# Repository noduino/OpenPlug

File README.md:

Noduino Open Plug
=======================================

[*Noduino Open Plug (OpenPlug V0.8)*](https://wiki.jackslab.org/Noduino_OpenPlug/)

[*Noduino Open Plug (OpenPlug V0.8)*](https://wiki.jackslab.org/Noduino_OpenPlug/)

Overview
-------------------

* AC 85V - 250V WiFi Smart Plug
* ESP8285 inside
* 250V 10A relay
* Shell size 53mm x 53mm x 27mm

Shell
-------------------

* https://detail.1688.com/offer/520959590805.html

WiFi Module
-------------------

[*Noduino NodeC WiFi Module*](https://wiki.jackslab.org/Noduino_SmartNode)

SCH
-------------------

[*Noduino Open Plug (OpenPlug V0.8)*](https://wiki.jackslab.org/Noduino_OpenPlug/)

Layout
-------------------

[*Noduino Open Plug (OpenPlug V0.8)*](https://wiki.jackslab.org/Noduino_OpenPlug/)

WiKi
-------------------

* http://wiki.jackslab.org/Noduino_OpenPlug

License Information
-------------------
The hardware is released under [Creative Commons ShareAlike 4.0 International](https://creativecommons.org/licenses/by-sa/4.0/).

Distributed as-is; no warranty is given.

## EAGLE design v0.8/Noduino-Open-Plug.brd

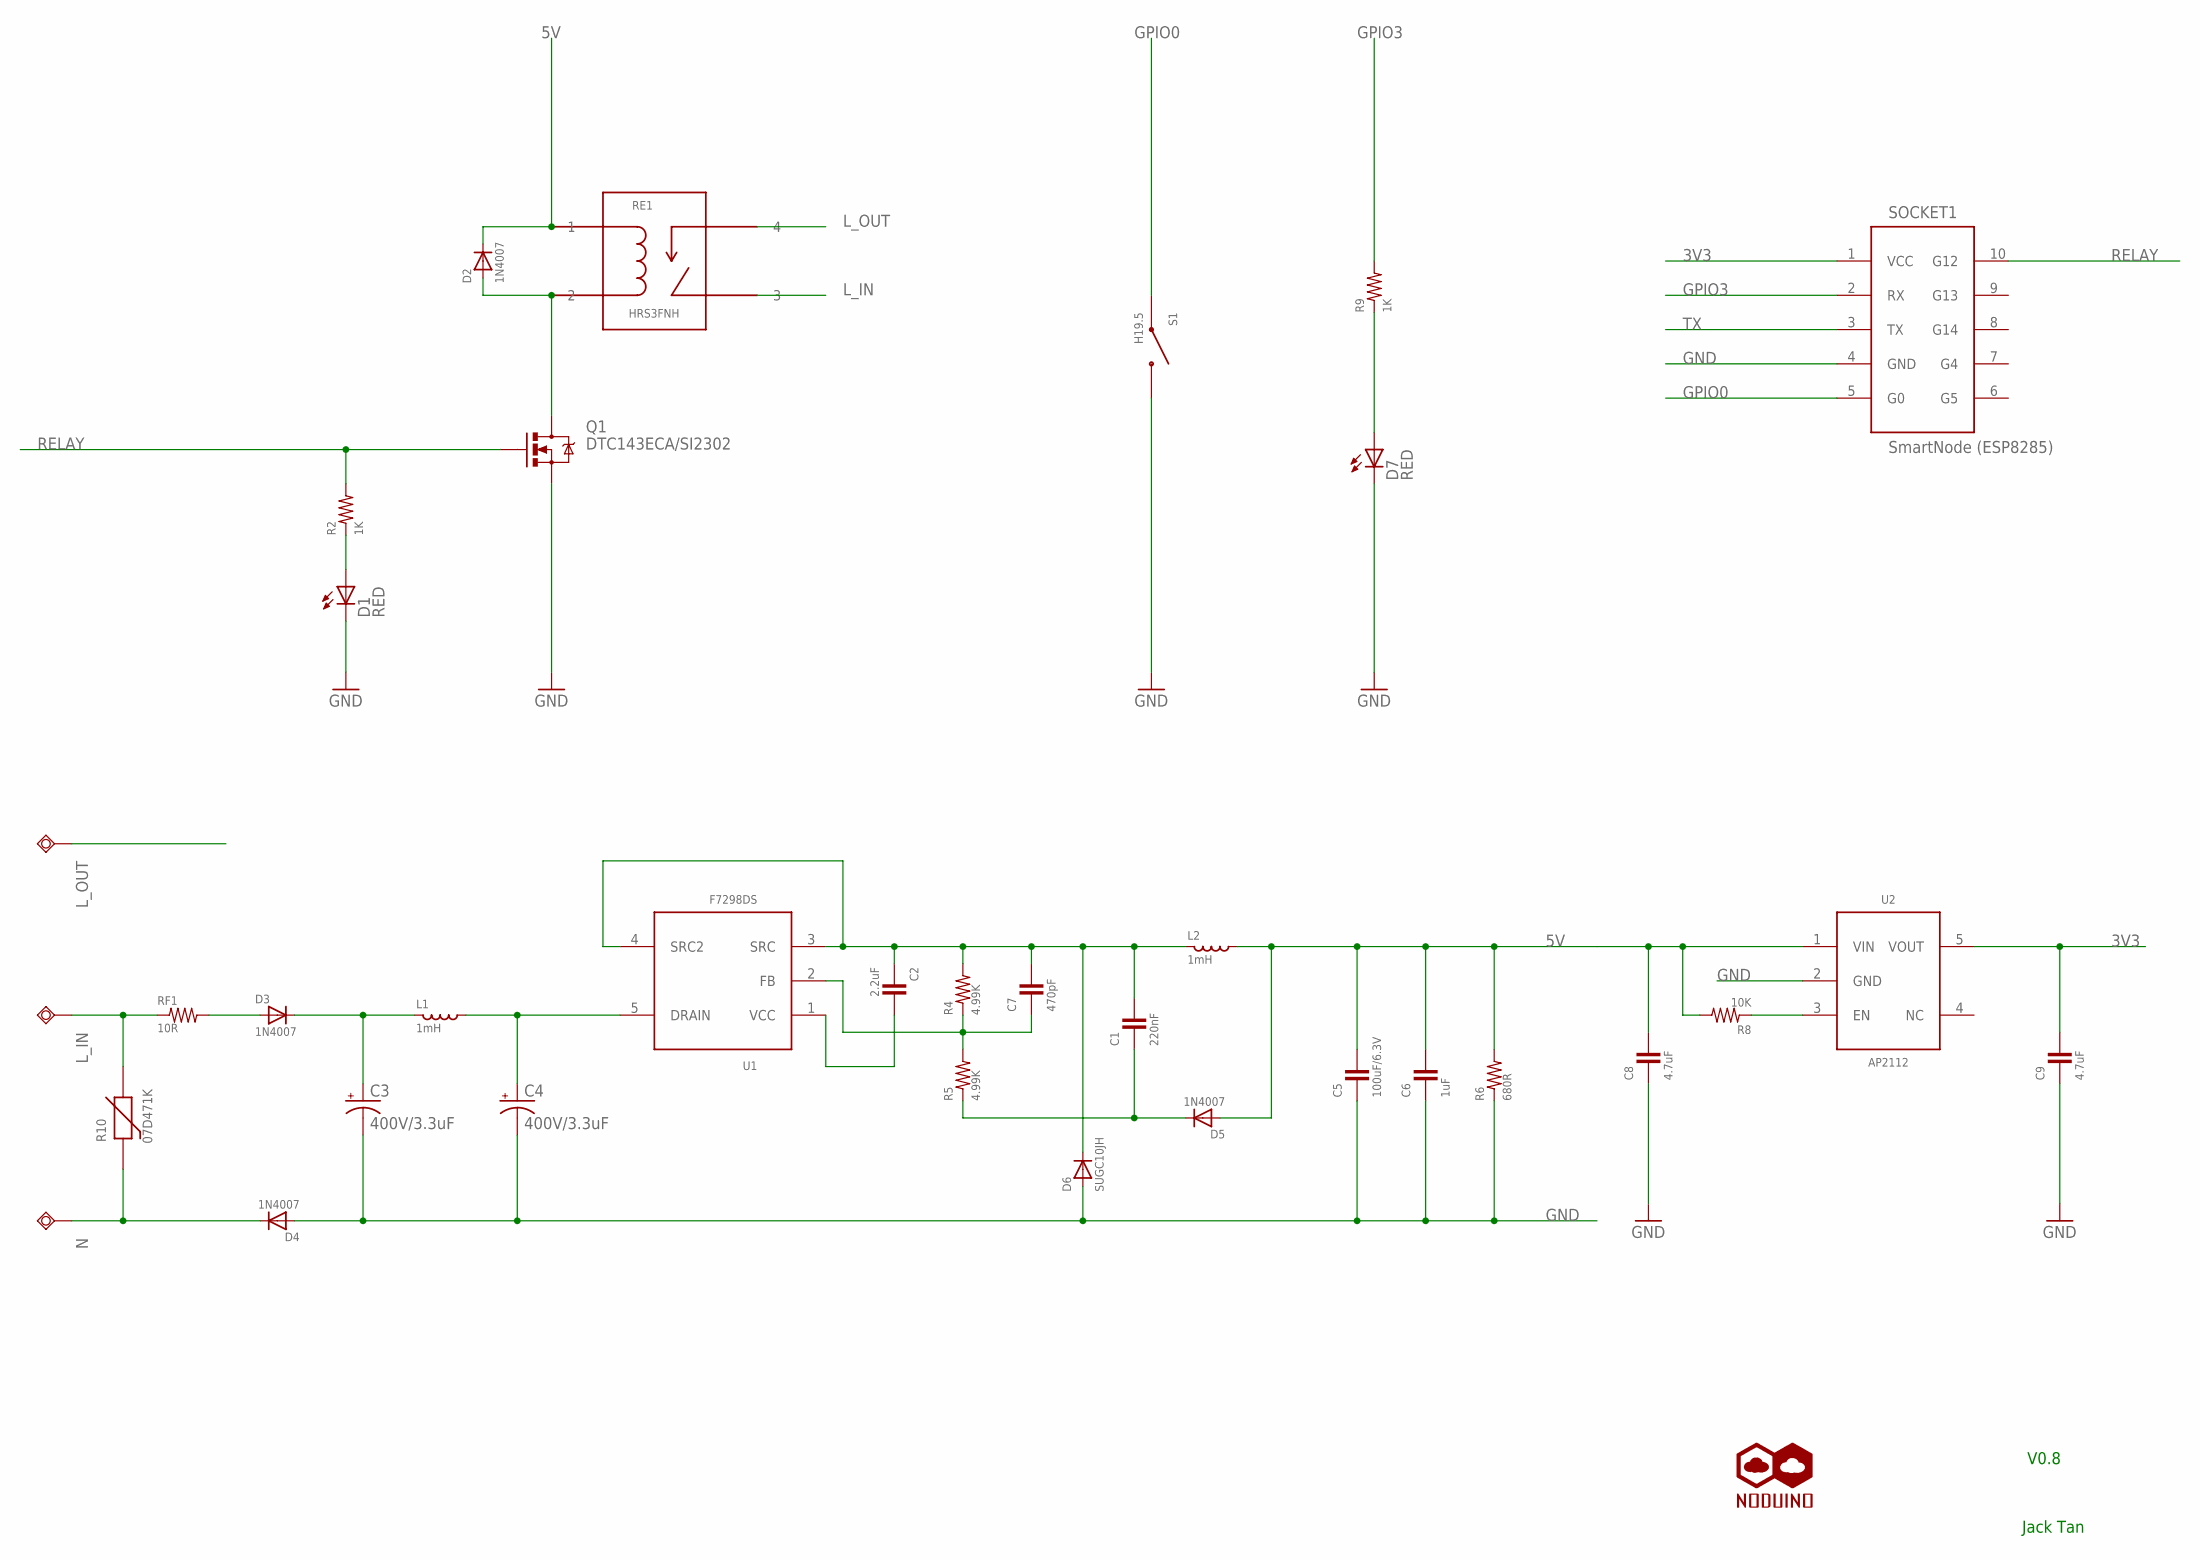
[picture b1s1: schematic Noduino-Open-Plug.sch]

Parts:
C1: 220nF; 0402-CAP
C2: 2.2uF; 0603-CAP
C3, C4: 400V/3.3uF; CPOL-RADIOA-3.3UF-400V
C5: 100uF/6.3V; B3528-CAP
C6: 1uF; 0402-CAP
C7: 470pF; 0402-CAP
C8, C9: 4.7uF; 0603-CAP
D1, D7: RED; LED3MM
D2: 1N4007; SOD-323
D3, D4, D5: 1N4007; DO-214
D6: SUGC10JH; SOD-123
L1: 1mH; 3-0.5-5
L2: 1mH; INDUCTOR-5-0.5
L_IN: TESTPAD50/25; 1SMD
L_OUT: TESTPAD50/25; 1SMD
N: TESTPAD50/25; 1SMD
Q1: DTC143ECA/SI2302; SOT23-3
R2, R9: 1K; 0603-RES
R4, R5: 4.99K; 0402-RES
R6: 680R; 0402-RES
R8: 10K; 0603-RES
R10: 07D471K
RE1: HRS3FNH; HKE-HRS3FN
RF1: 10R; 3-0.5-5
S1: H19.5; SWITCH-TS-037-PLUG
SOCKET1: SmartNode (ESP8285); MOD-PLUG-SOCKET
U1: F7298; SOT23-5
U2: AP2112; SOT23-5
U$1: NODUINO-LOGO-ALL; NODUINO-ALL-1

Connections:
3V3: C9.2, SOCKET1.1 (VCC), U2.5 (VOUT)
5V: C5.2, C6.2, C8.2, D2.1 (C), D5.A, L2.P$2 (X2), R6.2, R8.2, RE1.1, U2.1 (VIN)
GND: C3.P$2 (-), C4.P$2 (-), C5.1, C6.1, C8.1, C9.1, D1.K (C), D4.A, D6.A, D7.K (C), Q1.2 (S), R6.1, S1.P$1 (1), SOCKET1.4 (GND), U2.2 (GND)
GPIO0: S1.P$3 (2), SOCKET1.5 (G0)
GPIO3: R9.2, SOCKET1.2 (RX)
L_IN: L_IN.1, R10.P$2 (2), RE1.3, RF1.P$1 (1)
L_OUT: L_OUT.1, RE1.4
N: D4.C, N.1, R10.P$1 (1)
unnamed: D2.2 (A), Q1.3 (D), RE1.2
unnamed: C3.P$1 (+), D3.C, L1.P$1 (X1)
unnamed: D1.A, R2.1
unnamed: C4.P$1 (+), L1.P$2 (X2), U1.5 (DRAIN)
unnamed: C1.2, C2.1, C7.2, D6.C, L2.P$1 (X1), R4.2, U1.3 (SRC), U1.4 (SRC2)
unnamed: D3.A, RF1.P$2 (2)
unnamed: C2.2, U1.1 (VCC)
unnamed: C7.1, R4.1, R5.2, U1.2 (FB)
unnamed: C1.1, D5.C, R5.1
unnamed: R8.1, U2.3 (EN)
unnamed: D7.A, R9.1
RELAY: Q1.1 (G), R2.2, SOCKET1.10 (G12)
TX: SOCKET1.3 (TX)

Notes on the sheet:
Jack Tan
V0.8

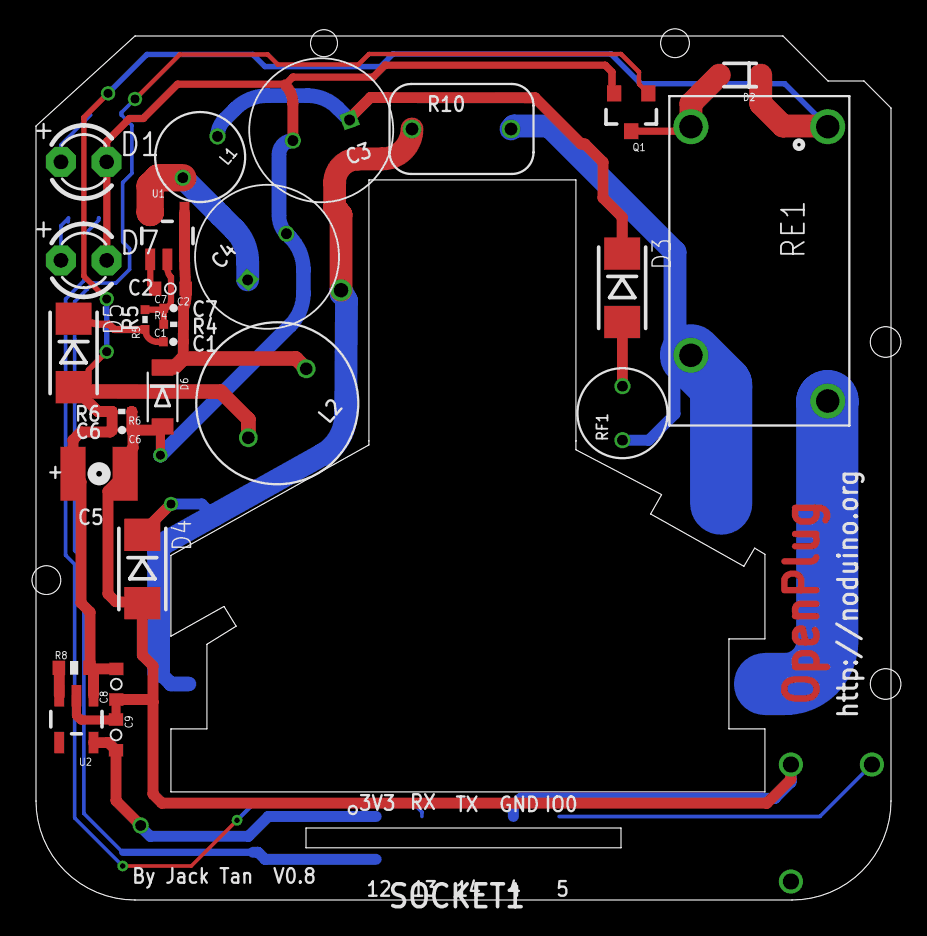
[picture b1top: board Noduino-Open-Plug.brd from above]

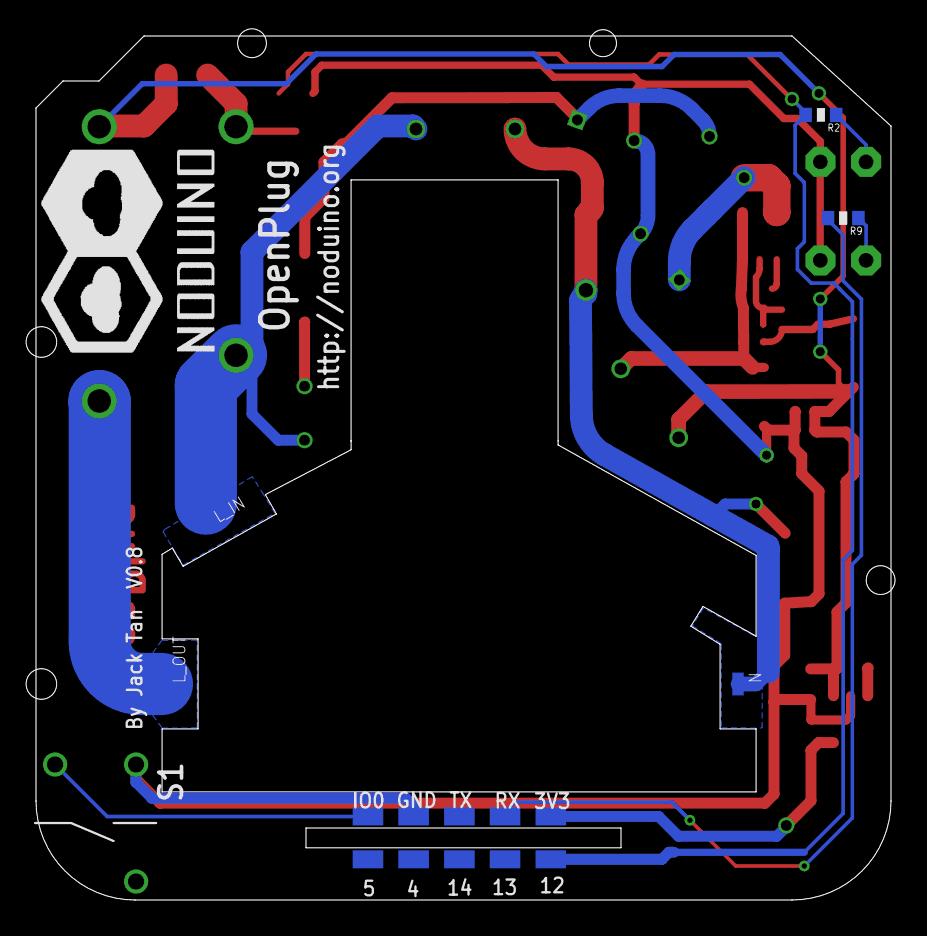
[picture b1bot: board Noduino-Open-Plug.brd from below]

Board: 2 copper layers, 47.5 x 48.0 mm, 36 parts (7 on the bottom side), 20 nets.

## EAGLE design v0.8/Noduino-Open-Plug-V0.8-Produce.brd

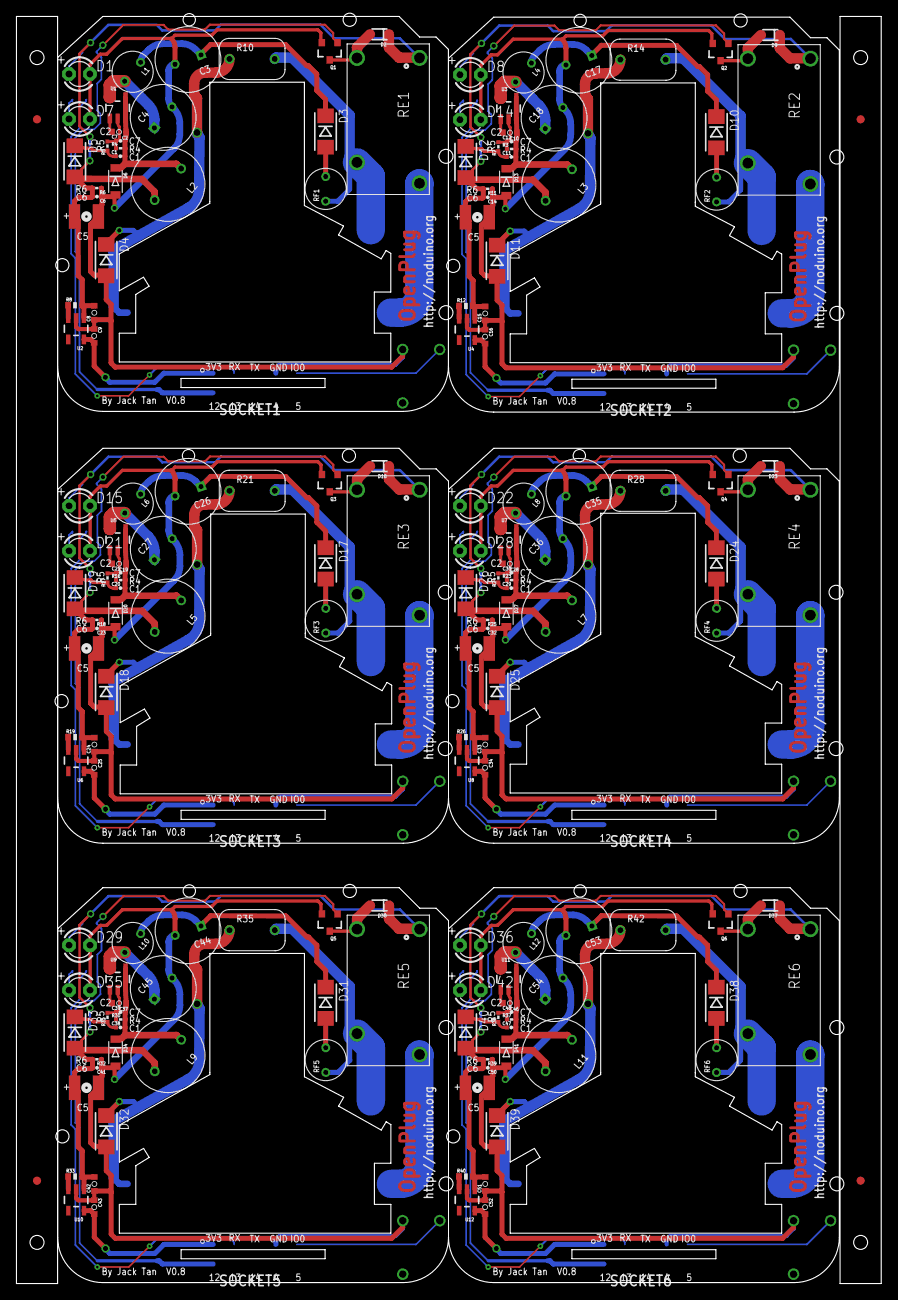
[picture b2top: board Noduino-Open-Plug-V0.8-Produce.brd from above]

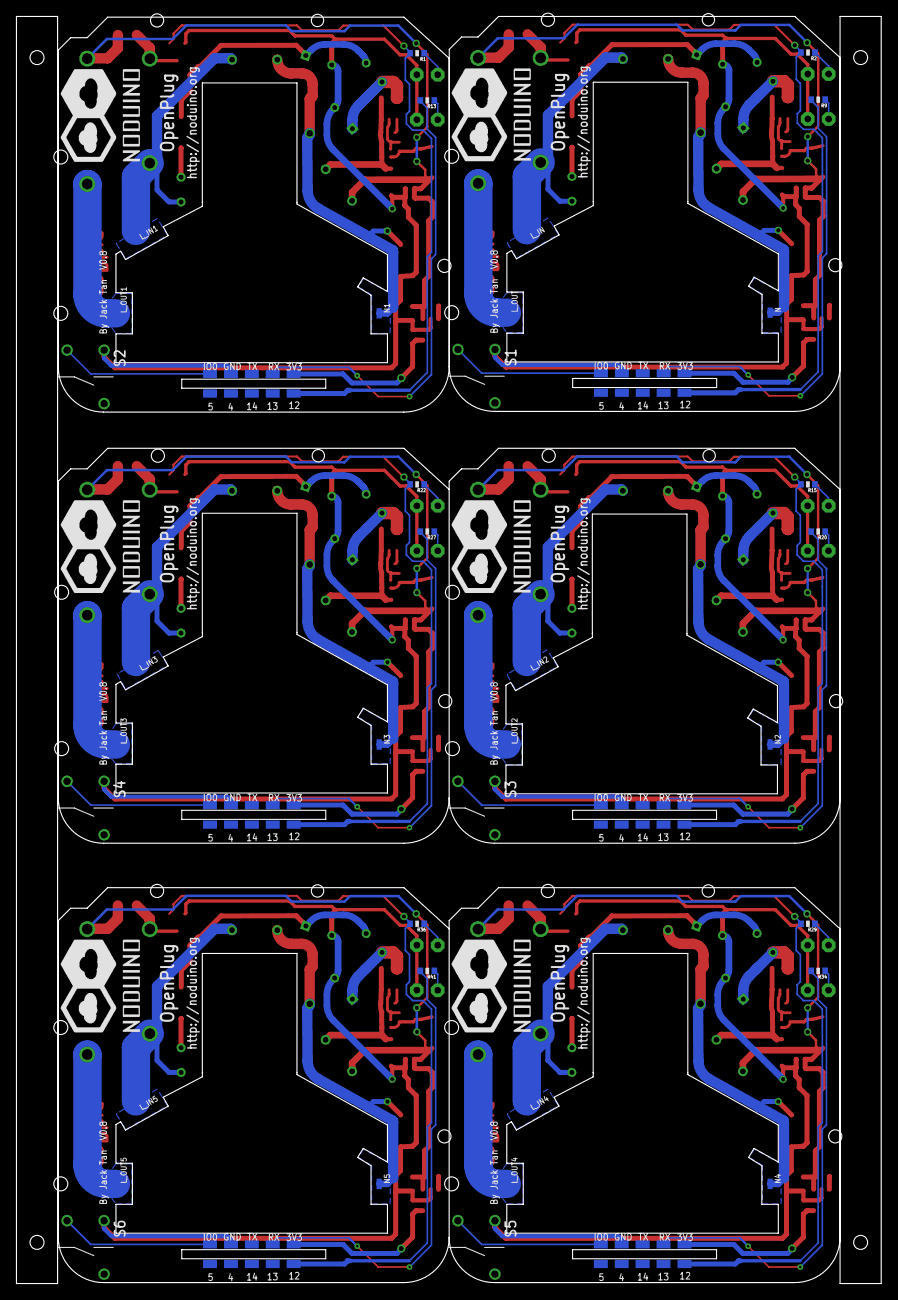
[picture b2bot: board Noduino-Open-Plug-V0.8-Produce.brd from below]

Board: 2 copper layers, 105.1 x 154.0 mm, 220 parts (42 on the bottom side), 120 nets.

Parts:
C1, C11, C20, C29, C38, C47: 220nF; 0402-CAP
C2, C10, C19, C28, C37, C46: 2.2uF; 0603-CAP
C3, C4, C17, C18, C26, C27, C35, C36, C44, C45, C53, C54: 400V/3.3uF; CPOL-RADIOA-3.3UF-400V
C5, C13, C22, C31, C40, C49: 100uF/6.3V; B3528-CAP
C6, C14, C23, C32, C41, C50: 1uF; 0402-CAP
C7, C12, C21, C30, C39, C48: 470pF; 0402-CAP
C8, C9, C15, C16, C24, C25, C33, C34, C42, C43, C51, C52: 4.7uF; 0603-CAP
D1, D7, D8, D14, D15, D21, D22, D28, D29, D35, D36, D42: RED; LED3MM
D2, D9, D16, D23, D30, D37: 1N4007; SOD-323
D3, D4, D5, D10, D11, D12, D17, D18, D19, D24, D25, D26, D31, D32, D33, D38, D39, D40: 1N4007; DO-214
D6, D13, D20, D27, D34, D41: T7; SOD-123
E$1, E$2, E$3, E$4: MARK-1MM
L1, L4, L6, L8, L10, L12: 1mH; 3-0.5-5
L2, L3, L5, L7, L9, L11: 1mH; INDUCTOR-5-0.5
L_IN, L_IN1, L_IN2, L_IN3, L_IN4, L_IN5: TESTPAD50/25; 1SMD
L_OUT, L_OUT1, L_OUT2, L_OUT3, L_OUT4, L_OUT5: TESTPAD50/25; 1SMD
N, N1, N2, N3, N4, N5: TESTPAD50/25; 1SMD
Q1, Q2, Q3, Q4, Q5, Q6: SI2302; SOT23-3
R1, R2, R9, R13, R15, R20, R22, R27, R29, R34, R36, R41: 1K; 0603-RES
R3, R4, R5, R7, R16, R17, R23, R24, R30, R31, R37, R38: 4.99K; 0402-RES
R6, R11, R18, R25, R32, R39: 680R; 0402-RES
R8, R12, R19, R26, R33, R40: 10K; 0603-RES
R10, R14, R21, R28, R35, R42: 07D471K
RE1, RE2, RE3, RE4, RE5, RE6: HRS3FNH; HKE-HRS3FN
RF1, RF2, RF3, RF4, RF5, RF6: 10R; 3-0.5-5
S1, S2, S3, S4, S5, S6: SWITCH-TS-037-PLUG
SOCKET1, SOCKET2, SOCKET3, SOCKET4, SOCKET5, SOCKET6: MOD-PLUG-SOCKET
U1, U3, U5, U7, U9, U11: F7298; SOT23-5
U2, U4, U6, U8, U10, U12: AP2112; SOT23-5
U$1, U$2, U$3, U$4, U$5, U$6: NODUINO-LOGO-ALL; NODUINO-ALL-1

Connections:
3V1: C16.2, SOCKET2.1, U4.5
3V2: C25.2, SOCKET3.1, U6.5
3V3: C9.2, SOCKET1.1, U2.5
3V4: C34.2, SOCKET4.1, U8.5
3V5: C43.2, SOCKET5.1, U10.5
3V6: C52.2, SOCKET6.1, U12.5
5V: C5.2, C6.2, C8.2, D2.1, D5.A, L2.P$2, R6.2, R8.2, RE1.1, U2.1
5V1: C13.2, C14.2, C15.2, D9.1, D12.A, L3.P$2, R11.2, R12.2, RE2.1, U4.1
5V2: C22.2, C23.2, C24.2, D16.1, D19.A, L5.P$2, R18.2, R19.2, RE3.1, U6.1
5V3: C31.2, C32.2, C33.2, D23.1, D26.A, L7.P$2, R25.2, R26.2, RE4.1, U8.1
5V4: C40.2, C41.2, C42.2, D30.1, D33.A, L9.P$2, R32.2, R33.2, RE5.1, U10.1
5V5: C49.2, C50.2, C51.2, D37.1, D40.A, L11.P$2, R39.2, R40.2, RE6.1, U12.1
GND: C3.P$2, C4.P$2, C5.1, C6.1, C8.1, C9.1, D1.K, D4.A, D6.A, D7.K, Q1.2, R6.1, S1.P$1, SOCKET1.4, U2.2
GND1: C13.1, C14.1, C15.1, C16.1, C17.P$2, C18.P$2, D8.K, D11.A, D13.A, D14.K, Q2.2, R11.1, S2.P$1, SOCKET2.4, U4.2
GND2: C22.1, C23.1, C24.1, C25.1, C26.P$2, C27.P$2, D15.K, D18.A, D20.A, D21.K, Q3.2, R18.1, S3.P$1, SOCKET3.4, U6.2
GND3: C31.1, C32.1, C33.1, C34.1, C35.P$2, C36.P$2, D22.K, D25.A, D27.A, D28.K, Q4.2, R25.1, S4.P$1, SOCKET4.4, U8.2
GND4: C40.1, C41.1, C42.1, C43.1, C44.P$2, C45.P$2, D29.K, D32.A, D34.A, D35.K, Q5.2, R32.1, S5.P$1, SOCKET5.4, U10.2
GND5: C49.1, C50.1, C51.1, C52.1, C53.P$2, C54.P$2, D36.K, D39.A, D41.A, D42.K, Q6.2, R39.1, S6.P$1, SOCKET6.4, U12.2
GPIO0: S1.P$3, SOCKET1.5
GPIO1: R13.2, SOCKET2.2
GPIO2: S2.P$3, SOCKET2.5
GPIO3: R9.2, SOCKET1.2
GPIO4: R20.2, SOCKET3.2
GPIO5: S3.P$3, SOCKET3.5
GPIO6: R27.2, SOCKET4.2
GPIO7: S4.P$3, SOCKET4.5
GPIO8: R34.2, SOCKET5.2
GPIO9: S5.P$3, SOCKET5.5
GPIO10: R41.2, SOCKET6.2
GPIO11: S6.P$3, SOCKET6.5
L_IN: L_IN.1, R10.P$2, RE1.3, RF1.P$1
L_IN1: L_IN1.1, R14.P$2, RE2.3, RF2.P$1
L_IN2: L_IN2.1, R21.P$2, RE3.3, RF3.P$1
L_IN3: L_IN3.1, R28.P$2, RE4.3, RF4.P$1
L_IN4: L_IN4.1, R35.P$2, RE5.3, RF5.P$1
L_IN5: L_IN5.1, R42.P$2, RE6.3, RF6.P$1
L_OUT: L_OUT.1, RE1.4
L_OUT1: L_OUT1.1, RE2.4
L_OUT2: L_OUT2.1, RE3.4
L_OUT3: L_OUT3.1, RE4.4
L_OUT4: L_OUT4.1, RE5.4
L_OUT5: L_OUT5.1, RE6.4
N: D4.C, N.1, R10.P$1
N1: D11.C, N1.1, R14.P$1
N2: D18.C, N2.1, R21.P$1
N3: D25.C, N3.1, R28.P$1
N4: D32.C, N4.1, R35.P$1
N5: D39.C, N5.1, R42.P$1
unnamed: D8.A, R1.1
unnamed: D2.2, Q1.3, RE1.2
unnamed: C3.P$1, D3.C, L1.P$1
unnamed: D1.A, R2.1
unnamed: C4.P$1, L1.P$2, U1.5
unnamed: C1.2, C2.1, C7.2, D6.C, L2.P$1, R4.2, U1.3, U1.4
unnamed: D3.A, RF1.P$2
unnamed: D9.2, Q2.3, RE2.2
unnamed: C17.P$1, D10.C, L4.P$1
unnamed: C2.2, U1.1
unnamed: C7.1, R4.1, R5.2, U1.2
unnamed: C1.1, D5.C, R5.1
unnamed: R8.1, U2.3
unnamed: D7.A, R9.1
unnamed: C18.P$1, L4.P$2, U3.5
unnamed: C10.1, C11.2, C12.2, D13.C, L3.P$1, R3.2, U3.3, U3.4
unnamed: D10.A, RF2.P$2
unnamed: C10.2, U3.1
unnamed: C12.1, R3.1, R7.2, U3.2
unnamed: C11.1, D12.C, R7.1
unnamed: R12.1, U4.3
unnamed: D14.A, R13.1
unnamed: D15.A, R15.1
unnamed: D16.2, Q3.3, RE3.2
unnamed: C26.P$1, D17.C, L6.P$1
unnamed: C27.P$1, L6.P$2, U5.5
unnamed: C19.1, C20.2, C21.2, D20.C, L5.P$1, R16.2, U5.3, U5.4
unnamed: D17.A, RF3.P$2
unnamed: C19.2, U5.1
unnamed: C21.1, R16.1, R17.2, U5.2
unnamed: C20.1, D19.C, R17.1
unnamed: R19.1, U6.3
unnamed: D21.A, R20.1
unnamed: D22.A, R22.1
unnamed: D23.2, Q4.3, RE4.2
unnamed: C35.P$1, D24.C, L8.P$1
unnamed: C36.P$1, L8.P$2, U7.5
unnamed: C28.1, C29.2, C30.2, D27.C, L7.P$1, R23.2, U7.3, U7.4
unnamed: D24.A, RF4.P$2
unnamed: C28.2, U7.1
unnamed: C30.1, R23.1, R24.2, U7.2
unnamed: C29.1, D26.C, R24.1
unnamed: R26.1, U8.3
unnamed: D28.A, R27.1
unnamed: D29.A, R29.1
unnamed: D30.2, Q5.3, RE5.2
unnamed: C44.P$1, D31.C, L10.P$1
unnamed: C45.P$1, L10.P$2, U9.5
unnamed: C37.1, C38.2, C39.2, D34.C, L9.P$1, R30.2, U9.3, U9.4
unnamed: D31.A, RF5.P$2
unnamed: C37.2, U9.1
unnamed: C39.1, R30.1, R31.2, U9.2
unnamed: C38.1, D33.C, R31.1
unnamed: R33.1, U10.3
unnamed: D35.A, R34.1
unnamed: D36.A, R36.1
unnamed: D37.2, Q6.3, RE6.2
unnamed: C53.P$1, D38.C, L12.P$1
unnamed: C54.P$1, L12.P$2, U11.5
unnamed: C46.1, C47.2, C48.2, D41.C, L11.P$1, R37.2, U11.3, U11.4
unnamed: D38.A, RF6.P$2
unnamed: C46.2, U11.1
unnamed: C48.1, R37.1, R38.2, U11.2
unnamed: C47.1, D40.C, R38.1
unnamed: R40.1, U12.3
unnamed: D42.A, R41.1
RELAY: Q1.1, R2.2, SOCKET1.10
RELAY1: Q2.1, R1.2, SOCKET2.10
RELAY2: Q3.1, R15.2, SOCKET3.10
RELAY3: Q4.1, R22.2, SOCKET4.10
RELAY4: Q5.1, R29.2, SOCKET5.10
RELAY5: Q6.1, R36.2, SOCKET6.10

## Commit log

2018-10-06 add the sch and layout files
2018-10-06 add the gerber files for mass producing
2018-10-06 update the readme
